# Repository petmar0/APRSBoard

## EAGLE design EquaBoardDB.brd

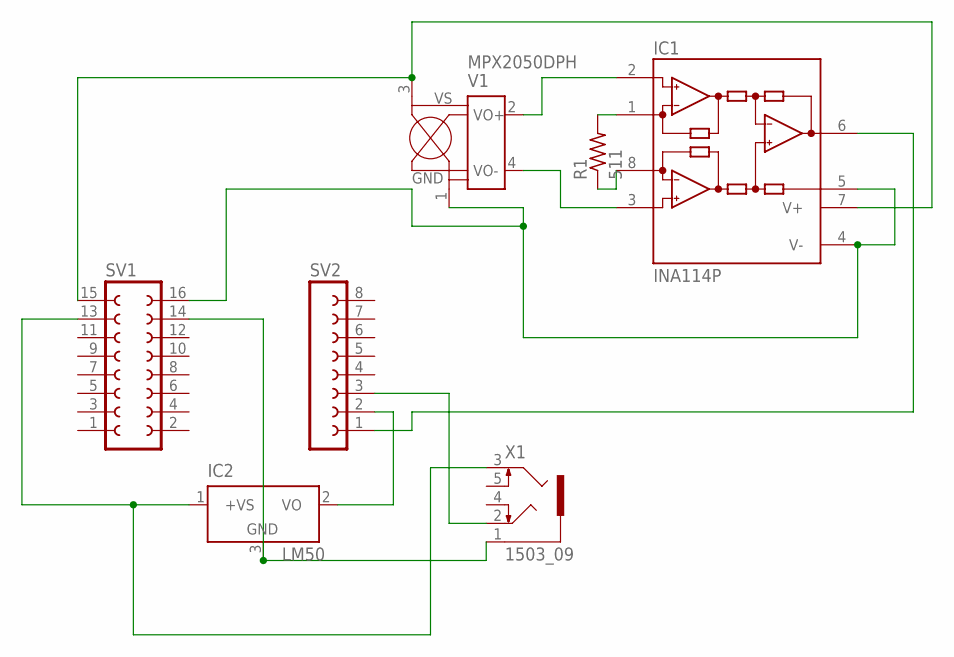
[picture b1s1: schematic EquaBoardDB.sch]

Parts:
IC1: INA114P; DIL08
IC2: LM50; SOT23
R1: 511; 0204/7
SV1: FE08-2
SV2: FE08-1; FE08
V1: MPX2050DPH
X1: 1503_09

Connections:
unnamed: IC1.2 (-IN), V1.2 (VO+)
unnamed: IC1.3 (+IN), V1.4 (VO-)
unnamed: IC1.1 (RG), R1.2
unnamed: IC1.8 (RG), R1.1
unnamed: IC1.4 (V-), IC1.5 (REF), SV1.16, V1.1 (GND)
unnamed: IC1.7 (V+), SV1.15, V1.3 (VS)
unnamed: IC1.6 (OUT), SV2.1
unnamed: IC2.1 (+VS), SV1.13, X1.3
unnamed: IC2.3 (GND), SV1.14, X1.1
unnamed: IC2.2 (VO), SV2.2
unnamed: SV2.3, X1.2

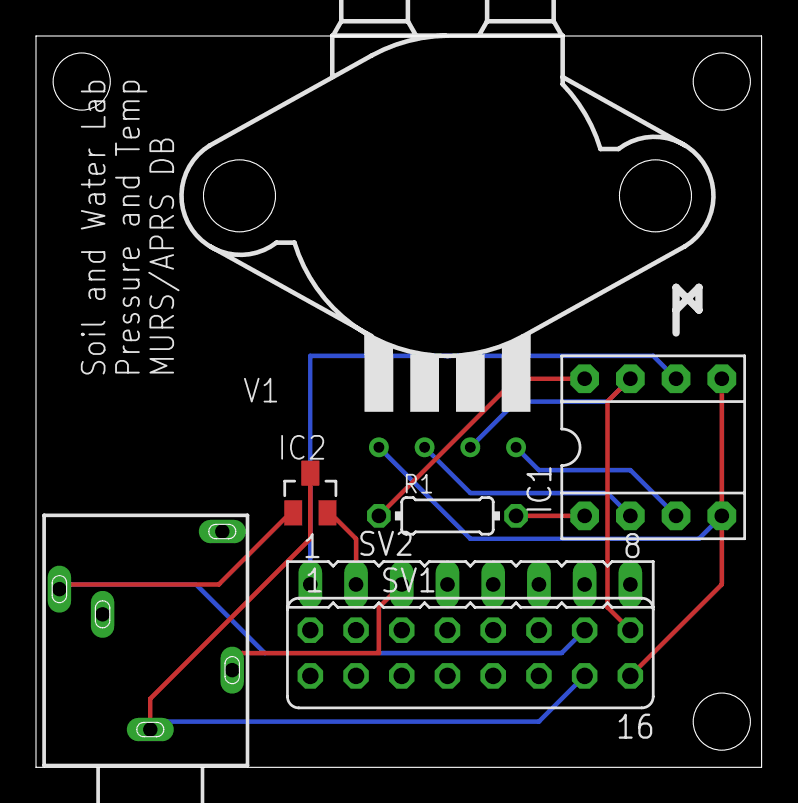
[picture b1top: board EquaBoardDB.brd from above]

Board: 2 copper layers, 40.3 x 40.6 mm, 7 parts (0 on the bottom side), 11 nets.

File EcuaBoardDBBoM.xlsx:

Part | Value | Device | Package | Description | MF | MPN | OC_FARNELL | OC_NEWARK
IC1 | INA114P | INA114P | DIL08 | Precision Instrumentation Amplifier | TEXAS INSTRUMENTS | INA114BP | 1212399 | 74K3810
IC2 | LM50 | LM50 | SOT23 | SOT-23 Single-Supply Centigrade Temperature Sensor
R1 | 511 | R-US_0204/7 | 0204/7 | RESISTOR, American symbol
SV1 |  | FE08-2 | FE08-2 | FEMALE HEADER |  |  | unknown | unknown
SV2 |  | FE08-1 | FE08 | FEMALE HEADER |  |  | unknown | unknown
V1 | MPX2050DPH | MPX2050DPH | MPX2050DPH | 50 kPa Pressure Sensor |  |  | unknown | unknown
X1 | 1503_09 | 1503_09 | 1503_09 | Jack connectors according to JISC 6560, 3.5 mm |  |  | 1243244 | unknown

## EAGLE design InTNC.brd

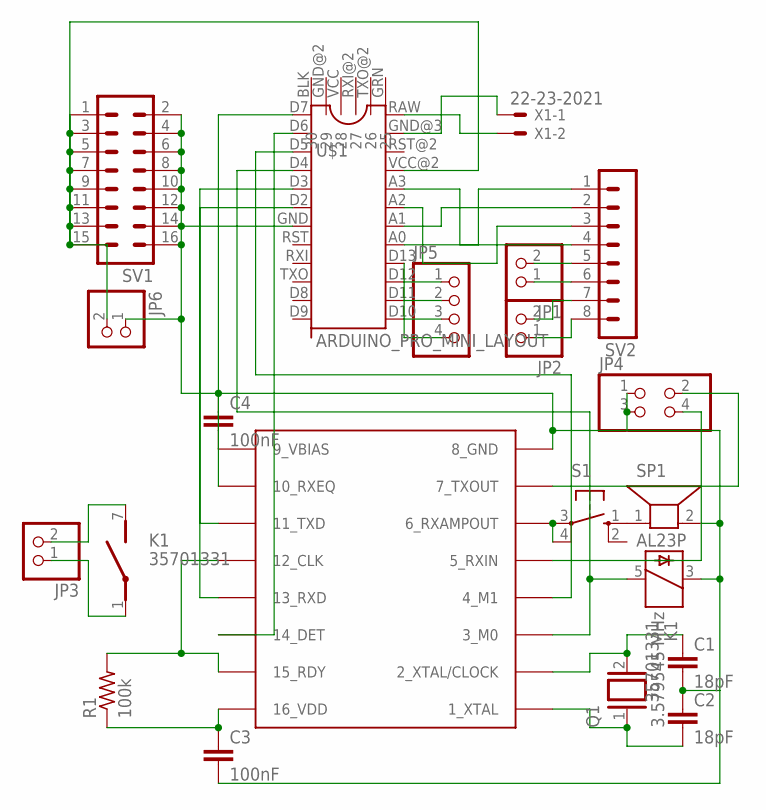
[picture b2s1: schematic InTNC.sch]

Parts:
C1, C2: 18pF; C2.5-2
C3, C4: 100nF; C2.5-2
JP1, JP2, JP3, JP6: PINHD-1X2; 1X02
JP4: PINHD-2X2; 2X02
JP5: PINHD-1X4; 1X04
K1: 35701331; REED
Q1: 3.579545 MHz; Q
R1: 100k; 0204/5
S1: 10-XX; B3F-10XX
SP1: AL23P
SV1: MA08-2
SV2: MA08-1
U$1: ARDUINO_PRO_MINI_LAYOUT; ARDUINO_PRO_MINI_PINOUT
U$2: MX614; SOIC16-3
X1: 22-23-2021

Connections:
unnamed: JP6.2, SV1.1, SV1.3, SV1.5, SV1.7, SV1.9, SV1.11, SV1.13, SV1.15, U$1.VCC@2 (21)
unnamed: C1.1, Q1.2, U$2.2 (2_XTAL/CLOCK)
unnamed: C2.2, Q1.1, U$2.1 (1_XTAL)
unnamed: C1.2, C2.1, C3.2, C4.1, JP4.1, JP4.3, JP6.1, K1.3, SP1.2, SV1.2, SV1.4, SV1.6, SV1.8, SV1.10, SV1.12, SV1.14, SV1.16, U$1.GND (7), U$2.8 (8_GND)
unnamed: K1.5, U$1.D4 (4), U$2.3 (3_M0)
unnamed: U$1.D5 (3), U$2.4 (4_M1)
unnamed: R1.2, U$2.12 (12_CLK), U$2.15 (15_RDY)
unnamed: C3.1, R1.1, U$2.16 (16_VDD)
unnamed: C4.2, U$2.9 (9_VBIAS)
unnamed: JP3.2, K1.7 (S)
unnamed: S1.3, S1.4 (P1), U$2.6 (6_RXAMPOUT)
unnamed: S1.1 (S), SP1.1
unnamed: JP3.1, K1.1
unnamed: JP4.4, U$2.5 (5_RXIN)
unnamed: JP4.2, U$2.7 (7_TXOUT)
unnamed: JP5.4, U$1.D10 (13)
unnamed: SV2.1, U$1.A0 (17)
unnamed: SV2.2, U$1.A1 (18)
unnamed: SV2.3, U$1.A2 (19)
unnamed: SV2.4, U$1.A3 (20)
unnamed: JP1.2, SV2.5
unnamed: JP1.1, SV2.6
unnamed: JP2.2, SV2.7
unnamed: JP2.1, SV2.8
unnamed: U$1.D2 (6), U$2.13 (13_RXD)
unnamed: U$1.D3 (5), U$2.11 (11_TXD)
unnamed: JP5.3, U$1.D11 (14)
unnamed: JP5.2, U$1.D12 (15)
unnamed: JP5.1, U$1.D13 (16)
unnamed: U$1.D6 (2), U$2.14 (14_DET)
unnamed: U$1.D7 (1), U$2.10 (10_RXEQ)
unnamed: U$1.RAW (24), X1.2
unnamed: U$1.GND@3 (23), X1.1

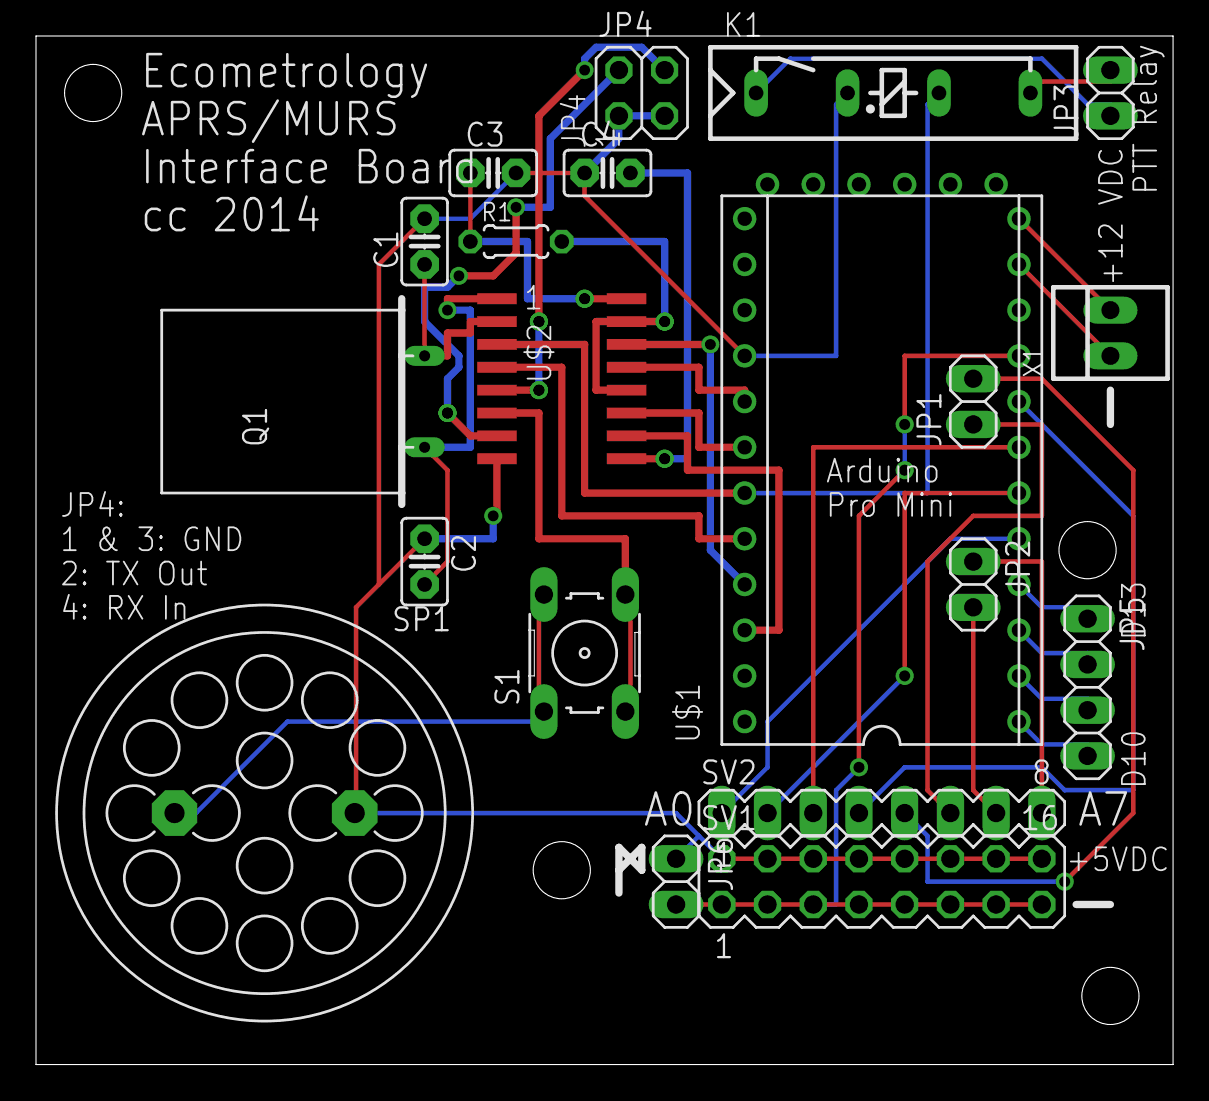
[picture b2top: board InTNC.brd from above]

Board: 2 copper layers, 63.2 x 57.1 mm, 20 parts (0 on the bottom side), 33 nets.

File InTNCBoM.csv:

"Part";"Value";"Device";"Package";"Description";"MF";"MPN";"OC_FARNELL";"OC_NEWARK";
"C1";"18pF";"C2.5/2";"C2.5-2";"CAPACITOR";"";"";"";"";
"C2";"18pF";"C2.5/2";"C2.5-2";"CAPACITOR";"";"";"";"";
"C3";"100nF";"C2.5/2";"C2.5-2";"CAPACITOR";"";"";"";"";
"C4";"100nF";"C2.5/2";"C2.5-2";"CAPACITOR";"";"";"";"";
"JP1";"";"PINHD-1X2";"1X02";"PIN HEADER";"";"";"";"";
"JP2";"";"PINHD-1X2";"1X02";"PIN HEADER";"";"";"";"";
"JP3";"";"PINHD-1X2";"1X02";"PIN HEADER";"";"";"";"";
"JP4";"";"PINHD-2X2";"2X02";"PIN HEADER";"";"";"";"";
"JP5";"";"PINHD-1X4";"1X04";"PIN HEADER";"";"";"";"";
"JP6";"";"PINHD-1X2";"1X02";"PIN HEADER";"";"";"";"";
"K1";"35701331";"35701331";"REED";"RELAY";"";"";"unknown";"unknown";
"Q1";"3.579545 MHz";"XTAL";"Q";"CRYSTAL";"";"";"";"";
"R1";"100k";"R-US_0204/5";"0204/5";"RESISTOR, American symbol";"";"";"";"";
"S1";"";"10-XX";"B3F-10XX";"OMRON SWITCH";"";"B3F-1000";"176432";"36M3542";
"SP1";"AL23P";"AL23P";"AL23P";"SPEAKER Source: Buerklin";"";"";"unknown";"unknown";
"SV1";"";"MA08-2";"MA08-2";"PIN HEADER";"";"";"unknown";"unknown";
"SV2";"";"MA08-1";"MA08-1";"PIN HEADER";"";"";"unknown";"unknown";
"U$1";"ARDUINO_PRO_MINI_LAYOUT";"ARDUINO_PRO_MINI_LAYOUT";"ARDUINO_PRO_MINI_PINOUT";"";"";"";"";"";
"U$2";"MX614";"MX614";"SOIC16-3";"";"";"";"";"";
"X1";"22-23-2021";"22-23-2021";"22-23-2021";".100" (2.54mm) Center Header - 2 Pin";"MOLEX";"22-23-2021";"1462926";"25C3832";

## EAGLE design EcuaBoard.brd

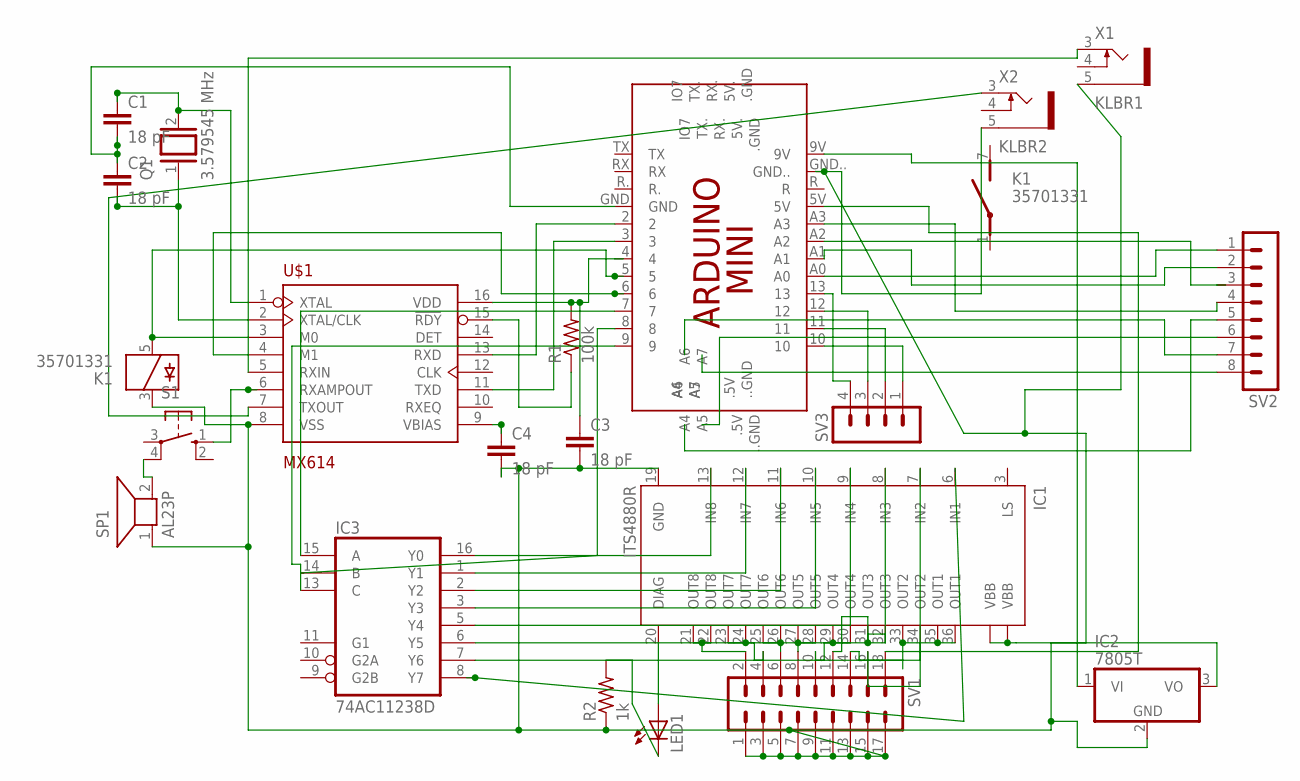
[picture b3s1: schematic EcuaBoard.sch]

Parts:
C1, C2, C3, C4: 18 pF; C2.5-2
IC1: ITS4880R; PG-DSO-36
IC2: 7805T; TO220H
IC3: 74AC11238D; SO16
K1: 35701331; REED
LED1: LED5MM
PCB1: ARDUINO_MINI
Q1: 3.579545 MHz; Q
R1: 100k; 0207/10
R2: 1k; 0207/10
S1: 10-XX; B3F-10XX
SP1: AL23P
SV1: MA09-2
SV2: MA08-1
SV3: MA04-1
U$1: MX614; SO16-1
X1: KLBR1
X2: KLBR2

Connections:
GND: IC3.4 (GND)
unnamed: IC1.21 (OUT8), IC1.22 (OUT8), SV1.2
unnamed: PCB1.5V, SV1.18
unnamed: C3.1, PCB1.4, R1.2, U$1.16 (VDD)
unnamed: IC1.23 (OUT7), IC1.24 (OUT7), SV1.4
unnamed: IC1.25 (OUT6), IC1.26 (OUT6), SV1.6
unnamed: IC1.27 (OUT5), IC1.28 (OUT5), SV1.8
unnamed: IC1.29 (OUT4), IC1.30 (OUT4), SV1.10
unnamed: PCB1.2, U$1.13 (RXD)
unnamed: PCB1.3, U$1.11 (TXD)
unnamed: K1.5, PCB1.5, U$1.3 (M0)
unnamed: PCB1.6, U$1.4 (M1)
unnamed: C2.2, Q1.1, U$1.2 (XTAL/CLK)
unnamed: C1.1, Q1.2, U$1.1 (XTAL)
unnamed: IC1.31 (OUT3), IC1.32 (OUT3), SV1.12
unnamed: C1.2, C2.1, PCB1.GND
unnamed: R1.1, U$1.15 (!RDY)
unnamed: C4.1, U$1.9 (VBIAS)
unnamed: IC2.1 (VI), PCB1.9V
unnamed: S1.4 (P1), SP1.2
unnamed: S1.1 (S), U$1.6 (RXAMPOUT)
unnamed: IC1.33 (OUT2), IC1.34 (OUT2), SV1.14
unnamed: U$1.7 (TXOUT), X2.3
unnamed: U$1.5 (RXIN), X1.3
unnamed: IC1.35 (OUT1), IC1.36 (OUT1), SV1.16
unnamed: IC1.TH@1 (VBB), IC1.TH@2 (VBB), IC2.3 (VO)
unnamed: IC1.20 (DIAG), LED1.A
unnamed: LED1.K (C), R2.2
unnamed: IC3.15 (A), PCB1.7
unnamed: IC3.14 (B), PCB1.8
unnamed: IC3.13 (C), PCB1.9
unnamed: IC1.13 (IN8), IC3.16 (Y0)
unnamed: IC1.12 (IN7), IC3.1 (Y1)
unnamed: IC1.11 (IN6), IC3.2 (Y2)
unnamed: IC1.10 (IN5), IC3.3 (Y3)
unnamed: IC1.9 (IN4), IC3.5 (Y4)
unnamed: IC1.8 (IN3), IC3.6 (Y5)
unnamed: IC1.7 (IN2), IC3.7 (Y6)
unnamed: IC1.6 (IN1), IC3.8 (Y7)
unnamed: PCB1.A0, SV2.1
unnamed: PCB1.A1, SV2.2
unnamed: PCB1.A3, SV2.4
unnamed: PCB1.10, SV3.1
unnamed: PCB1.11, SV3.2
unnamed: PCB1.12, SV3.3
unnamed: PCB1.13, SV3.4
VCC: IC3.12 (VCC)
VSS: C3.2, C4.2, IC1.19 (GND), IC2.2 (GND), K1.3, PCB1.GND.., R2.1, SP1.1, SV1.1, SV1.3, SV1.5, SV1.7, SV1.9, SV1.11, SV1.13, SV1.15, SV1.17, U$1.8 (VSS), X1.5, X2.5

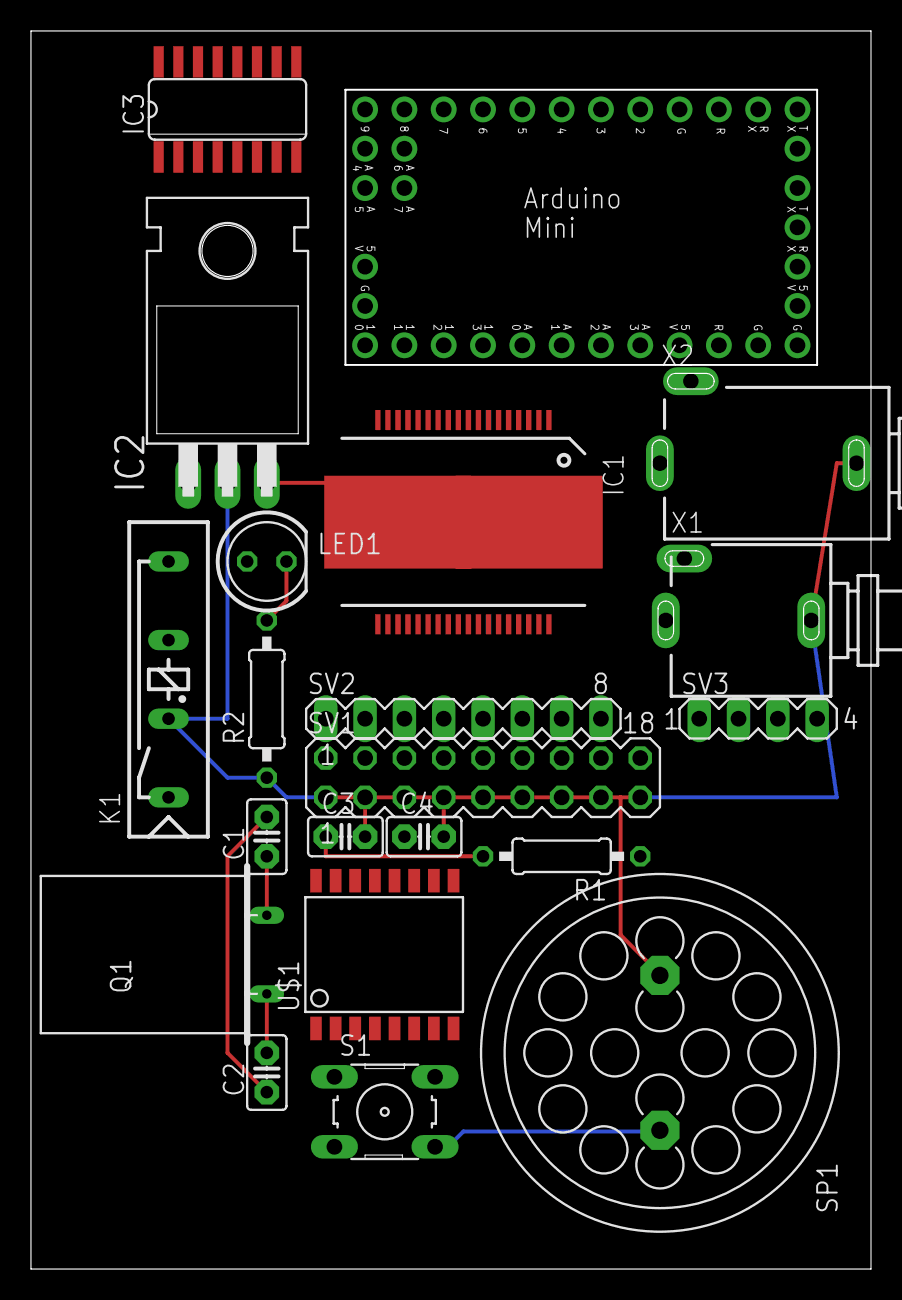
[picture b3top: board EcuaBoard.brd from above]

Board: 2 copper layers, 54.2 x 79.9 mm, 21 parts (0 on the bottom side), 46 nets.

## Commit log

2014-11-12 Fixed delay bug
